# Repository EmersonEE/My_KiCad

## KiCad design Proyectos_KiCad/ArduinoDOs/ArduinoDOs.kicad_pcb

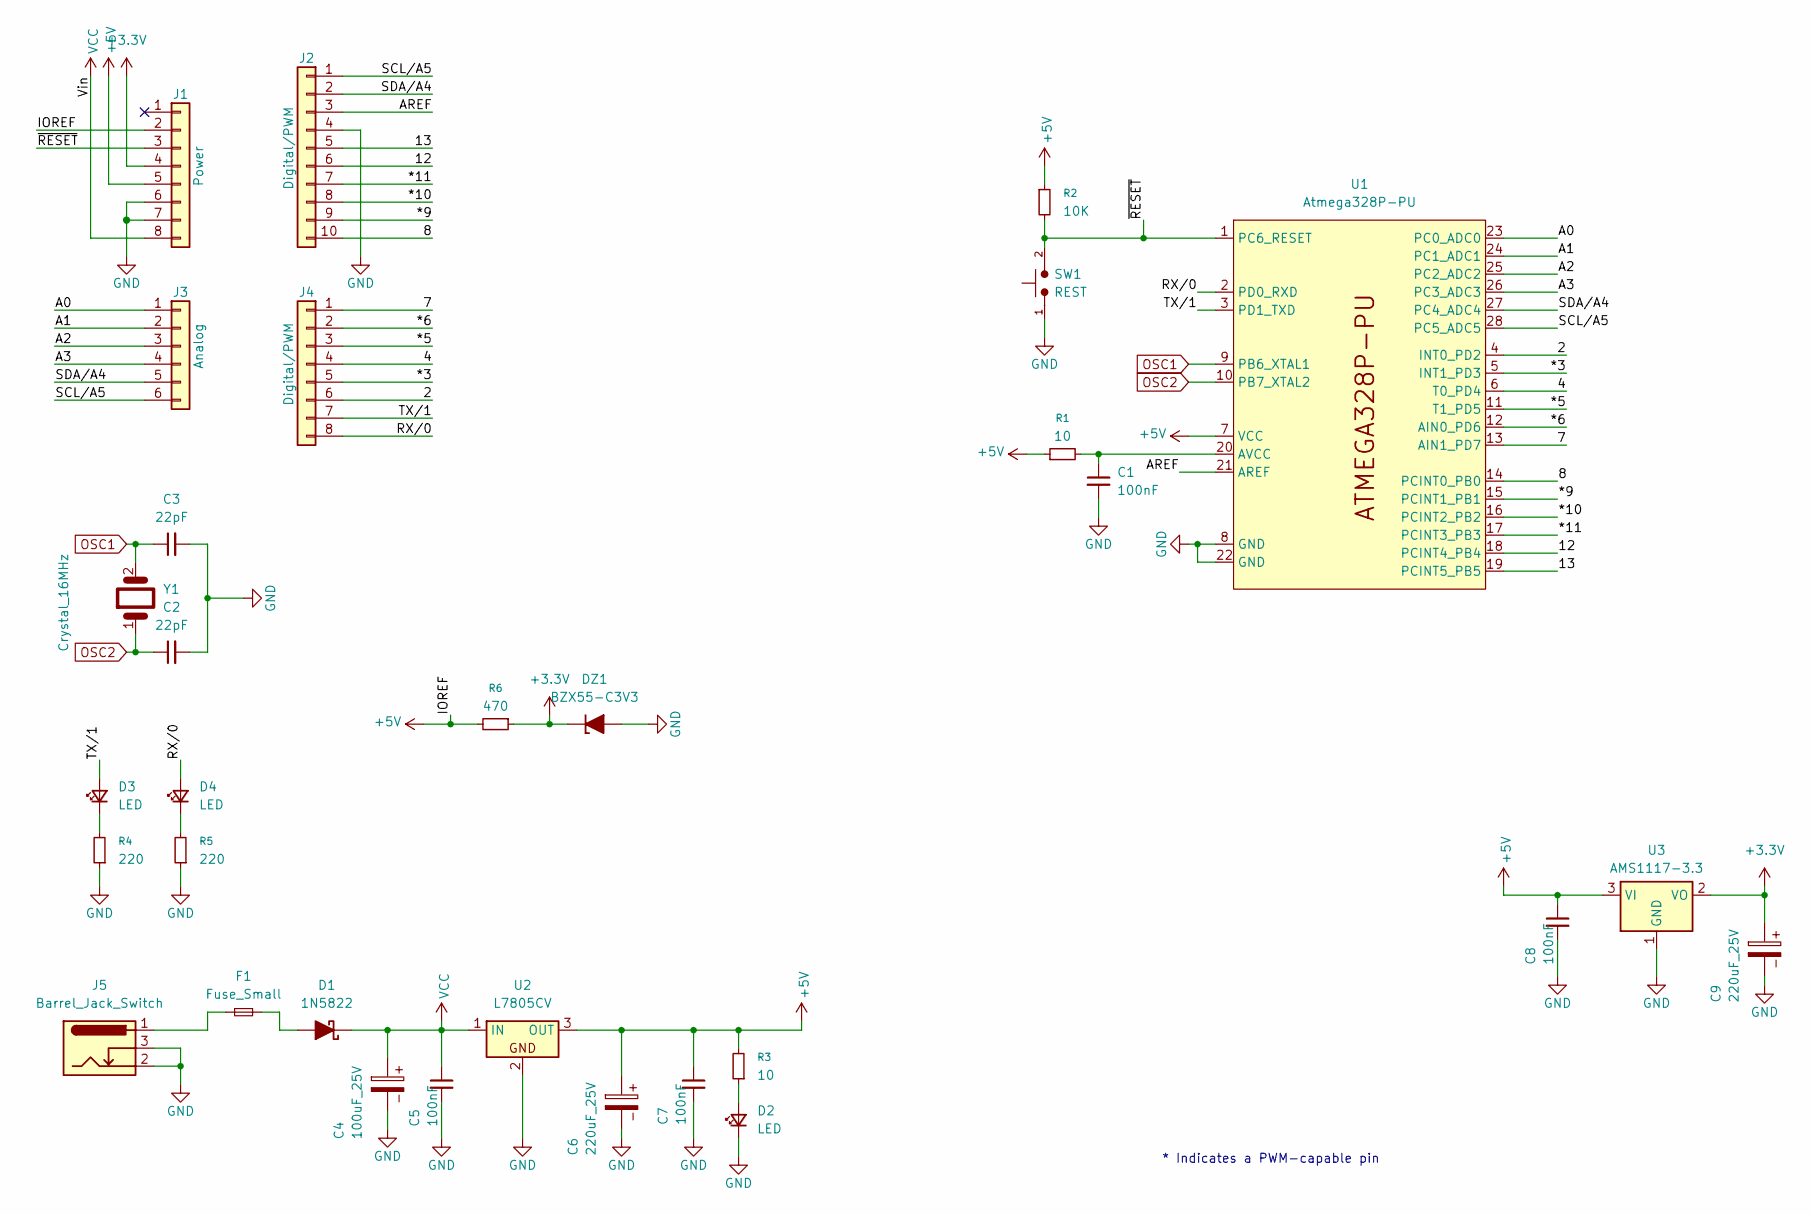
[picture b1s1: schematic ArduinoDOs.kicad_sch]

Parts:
C1, C5, C7, C8: 100nF; C_Disc_D4.7mm_W2.5mm_P5.00mm
C2, C3: 22pF; C_Disc_D4.7mm_W2.5mm_P5.00mm
C4: 100uF_25V; CP_Radial_D6.3mm_P2.50mm
C6, C9: 220uF_25V; CP_Radial_D8.0mm_P3.50mm
D1: 1N5822; D_DO-201AD_P12.70mm_Horizontal
D2, D3, D4: LED; LED_D5.0mm
DZ1: BZX55-C3V3; D_DO-35_SOD27_P7.62mm_Horizontal_Zener
F1: Fuse_Small; Fuse_BelFuse_0ZRE0033FF_L11.4mm_W3.8mm
J1: Power; PinSocket_1x08_P2.54mm_Vertical
J2: Digital/PWM; PinSocket_1x10_P2.54mm_Vertical
J3: Analog; PinSocket_1x06_P2.54mm_Vertical
J4: Digital/PWM; PinSocket_1x08_P2.54mm_Vertical
J5: Barrel_Jack_Switch; BarrelJack_GCT_DCJ200-10-A_Horizontal
R1, R3: 10; R_Axial_DIN0207_L6.3mm_D2.5mm_P10.16mm_Horizontal
R2: 10K; R_Axial_DIN0207_L6.3mm_D2.5mm_P10.16mm_Horizontal
R4, R5: 220; R_Axial_DIN0207_L6.3mm_D2.5mm_P10.16mm_Horizontal
R6: 470; R_Axial_DIN0207_L6.3mm_D2.5mm_P10.16mm_Horizontal
SW1: REST; SW_PUSH_6mm
U1: Atmega328P-PU; CERDIP-28_W7.62mm_SideBrazed_LongPads
U2: L7805CV; TO-220-3_Vertical
U3: AMS1117-3.3; SOT-223-3_TabPin2
Y1: Crystal_16MHz; Crystal_HC49-4H_Vertical

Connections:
+3.3V: C9.1, DZ1.1 (K), J1.4, R6.1, U3.2 (VO)
+5V: C6.1, C7.1, C8.1, J1.2, J1.5, R1.1, R2.1, R3.2, R6.2, U1.7 (VCC), U2.3 (OUT), U3.3 (VI)
/2: J4.6, U1.4 (INT0_PD2)
/4: J4.4, U1.6 (T0_PD4)
/7: J4.1, U1.13 (AIN1_PD7)
/8: J2.10, U1.14 (PCINT0_PB0)
/12: J2.6, U1.18 (PCINT4_PB4)
/13: J2.5, U1.19 (PCINT5_PB5)
/*3: J4.5, U1.5 (INT1_PD3)
/*5: J4.3, U1.11 (T1_PD5)
/*6: J4.2, U1.12 (AIN0_PD6)
/*9: J2.9, U1.15 (PCINT1_PB1)
/*10: J2.8, U1.16 (PCINT2_PB2)
/*11: J2.7, U1.17 (PCINT3_PB3)
/A0: J3.1, U1.23 (PC0_ADC0)
/A1: J3.2, U1.24 (PC1_ADC1)
/A2: J3.3, U1.25 (PC2_ADC2)
/A3: J3.4, U1.26 (PC3_ADC3)
/AREF: J2.3, U1.21 (AREF)
/RX/0: D4.2 (A), J4.8, U1.2 (PD0_RXD)
/SCL/A5: J2.1, J3.6, U1.28 (PC5_ADC5)
/SDA/A4: J2.2, J3.5, U1.27 (PC4_ADC4)
/TX/1: D3.2 (A), J4.7, U1.3 (PD1_TXD)
/~RESET: J1.3, R2.2, SW1.2, U1.1 (PC6_RESET)
GND: C1.2, C2.2, C3.2, C4.2, C5.2, C6.2, C7.2, C8.2, C9.2, D2.1 (K), DZ1.2 (A), J1.6, J1.7, J2.4, J5.2, J5.3, R4.1, R5.1, SW1.1, U1.8 (GND), U1.22 (GND), U2.2, U3.1 (GND)
unnamed: D1.2 (A), F1.2
unnamed: D2.2 (A), R3.1
unnamed: D3.1 (K), R4.2
unnamed: D4.1 (K), R5.2
unnamed: F1.1, J5.1
unnamed: C1.1, R1.2, U1.20 (AVCC)
OSC1: C3.1, U1.9 (PB6_XTAL1), Y1.2
OSC2: C2.1, U1.10 (PB7_XTAL2), Y1.1
VCC: C4.1, C5.1, D1.1 (K), J1.8, U2.1 (IN)

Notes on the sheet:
* Indicates a PWM-capable pin

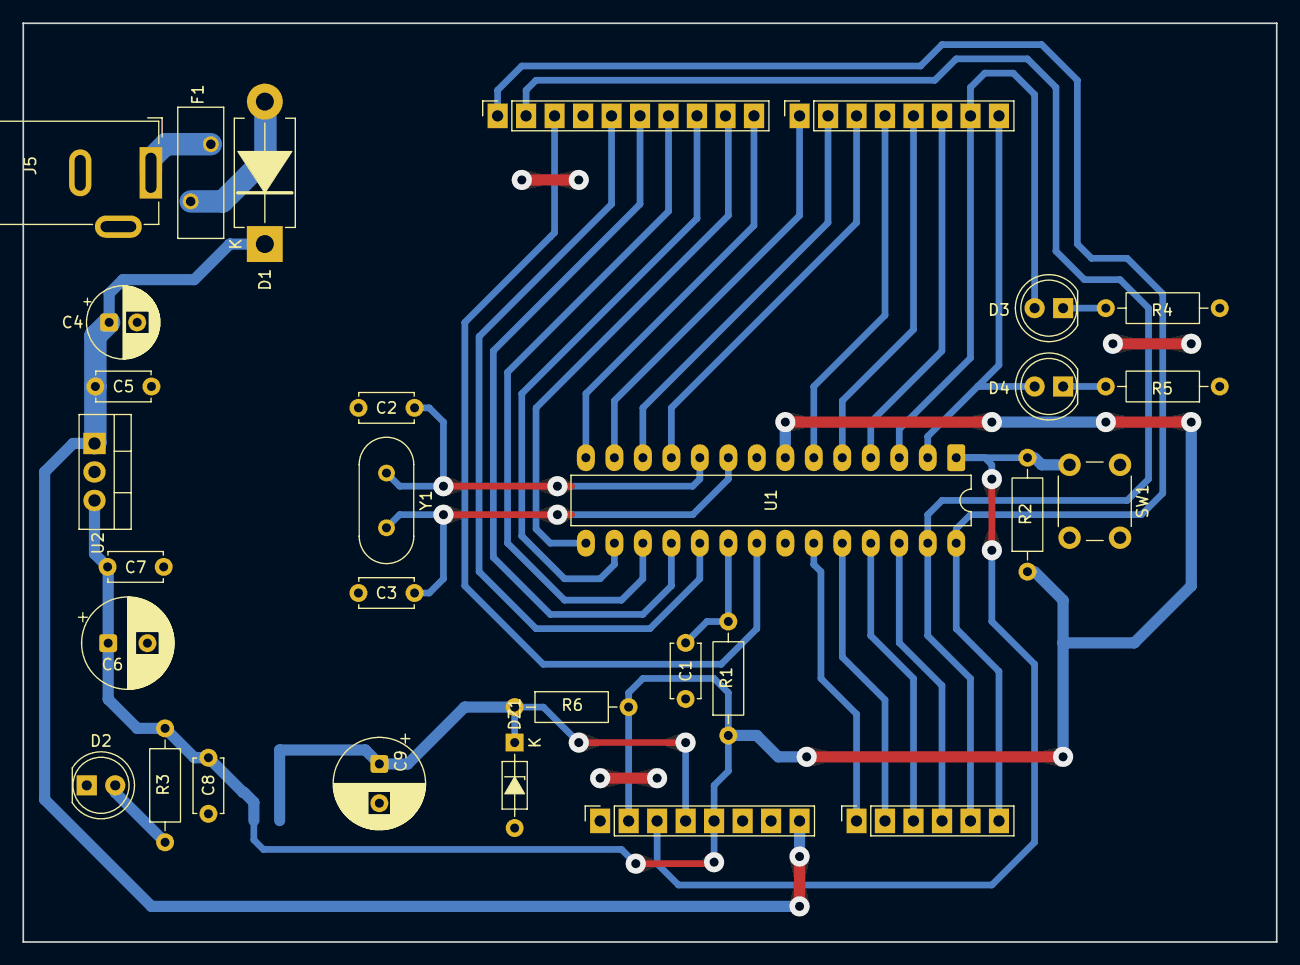
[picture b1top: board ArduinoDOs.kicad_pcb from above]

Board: 2 copper layers, 111.8 x 81.9 mm, 31 parts (1 on the bottom side), 34 nets.

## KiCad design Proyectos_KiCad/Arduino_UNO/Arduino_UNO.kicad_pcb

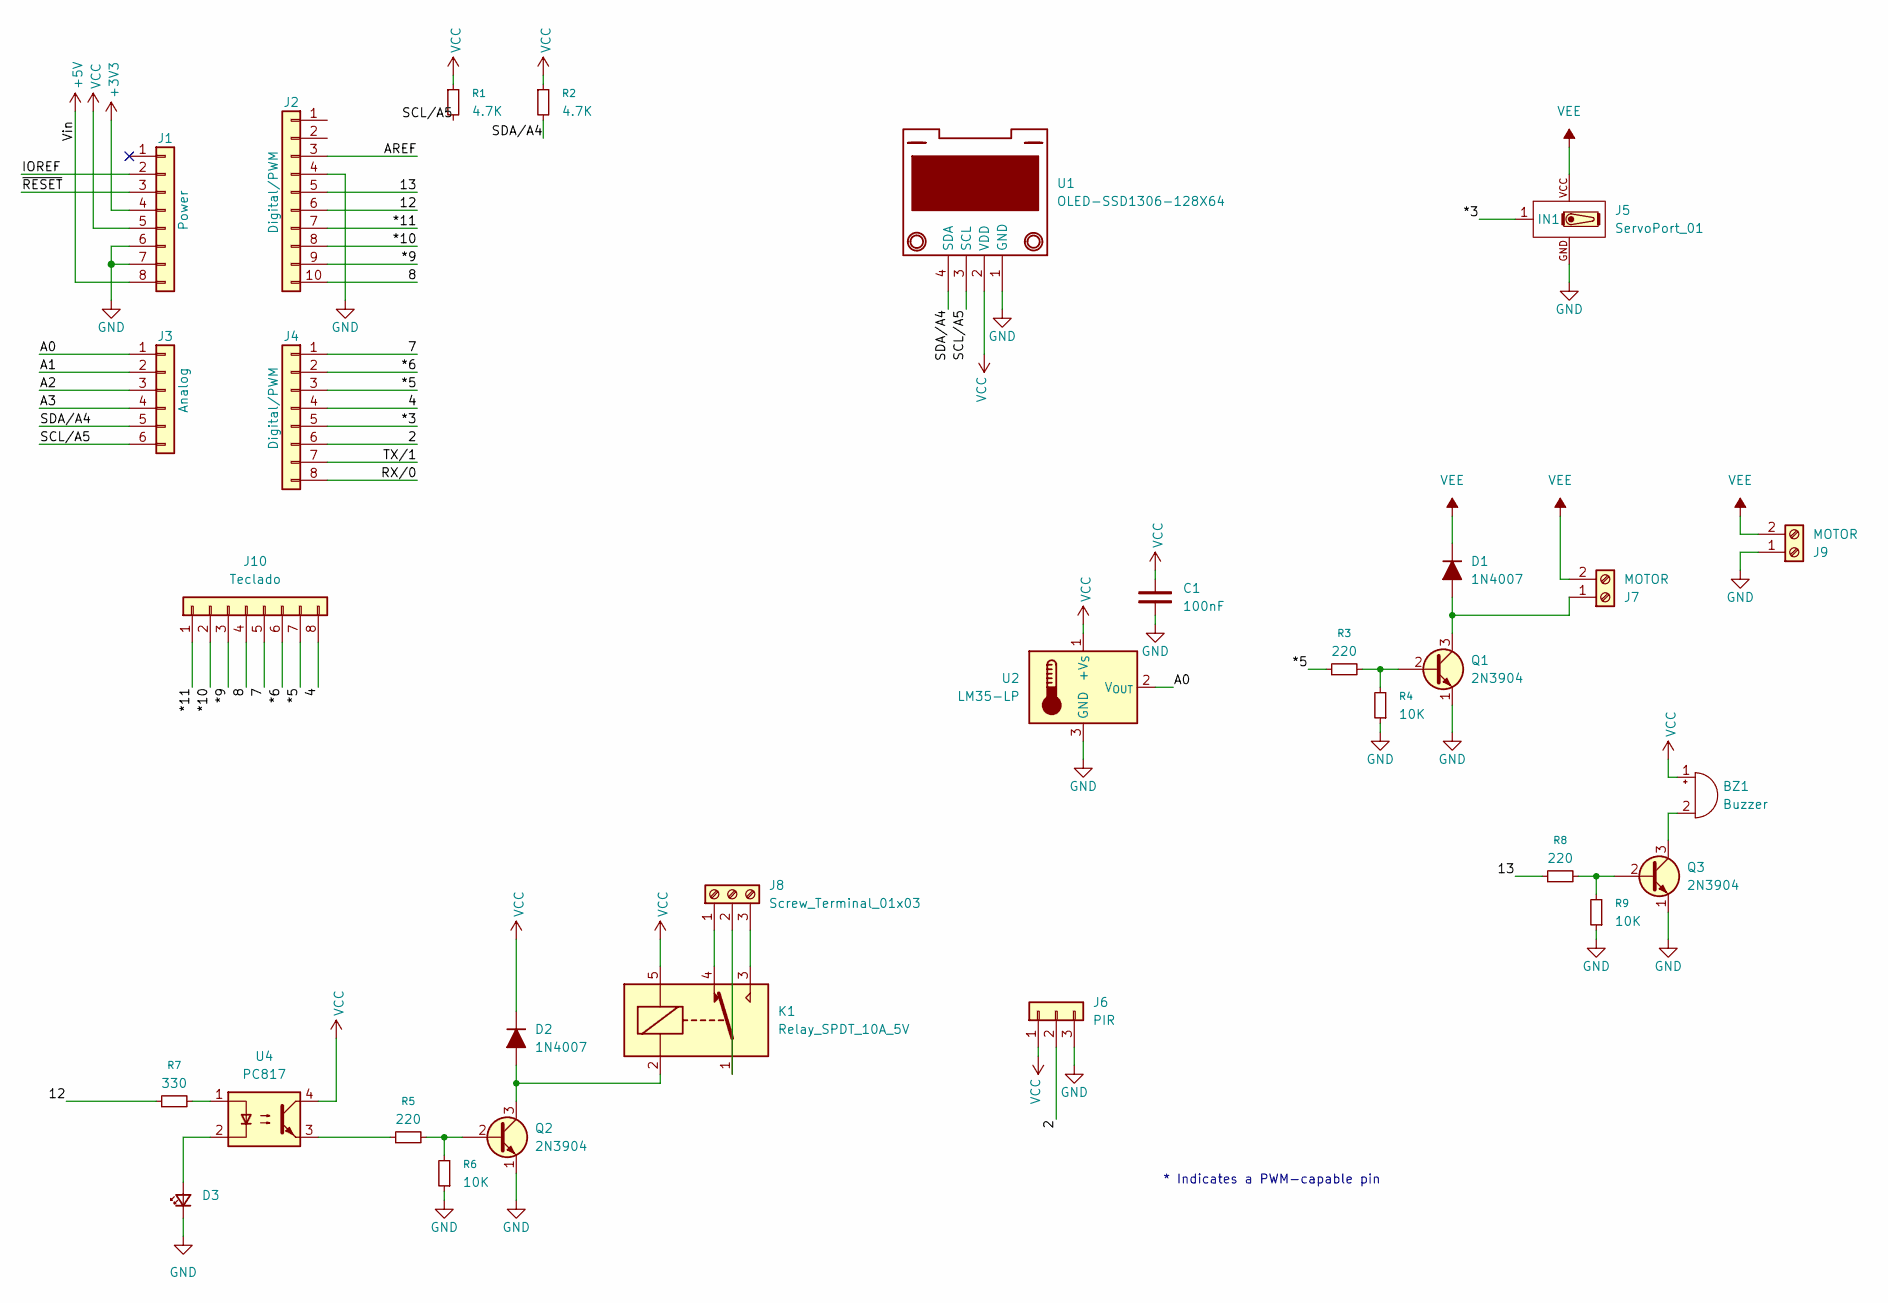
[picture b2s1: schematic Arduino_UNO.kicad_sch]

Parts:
BZ1: Buzzer; MagneticBuzzer_ProSignal_ABT-410-RC
C1: 100nF; C_Disc_D5.0mm_W2.5mm_P2.50mm
D1, D2: 1N4007; D_DO-41_SOD81_P7.62mm_Horizontal
D3: LED_D5.0mm
J1: Power; PinHeader_1x08_P2.54mm_Vertical
J2: Digital/PWM; PinHeader_1x10_P2.54mm_Vertical
J3: Analog; PinHeader_1x06_P2.54mm_Vertical
J4: Digital/PWM; PinHeader_1x08_P2.54mm_Vertical
J5: ServoPort_01; ServoPort_01_Vertical
J6: PIR; PinHeader_1x03_P2.54mm_Vertical
J7, J9: MOTOR; TerminalBlock_Phoenix_MKDS-1,5-2-5.08_1x02_P5.08mm_Horizont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
J8: Screw_Terminal_01x03; TerminalBlock_Phoenix_MKDS-1,5-3_1x03_P5.00mm_Horizontal
J10: Teclado; PinHeader_1x08_P2.54mm_Vertical
K1: Relay_SPDT_10A_5V; Relay_SPDT_10A_15.2x19.0mm
Q1, Q2, Q3: 2N3904; TO-92_Inline_Wide_EBC
R1, R2: 4.7K; 2.2
R3, R5, R8: 220; 2.2
R4, R6, R9: 10K; 2.2
R7: 330; 2.2
U1: OLED-SSD1306-128X64; SSD1306
U2: LM35-LP; TO-92L_Inline_Wide
U4: PC817; DIP-4_W7.62mm

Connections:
+3V3: J1.4
+5V: J1.8
/2: J4.6, J6.2
/4: J4.4, J10.8
/7: J4.1, J10.5
/8: J2.10, J10.4
/12: J2.6, R7.1
/13: J2.5, R8.1
/*3: J4.5, J5.1 (IN1_1)
/*5: J4.3, J10.7, R3.1
/*6: J4.2, J10.6
/*9: J2.9, J10.3
/*10: J2.8, J10.2
/*11: J2.7, J10.1
/A0: J3.1, U2.2 (V_{OUT})
/A1: J3.2
/A2: J3.3
/A3: J3.4
/AREF: J2.3
/IOREF: J1.2
/RX/0: J4.8
/SCL/A5: J3.6, R1.2, U1.3 (SCL)
/SDA/A4: J3.5, R2.2, U1.4 (SDA)
/TX/1: J4.7
/~RESET: J1.3
GND: C1.1, D3.1 (K), J1.6, J1.7, J2.4, J5.GND, J6.3, J9.1, Q1.1 (E), Q2.1 (E), Q3.1 (E), R4.1, R6.1, R9.1, U1.1 (GND), U2.3 (GND)
unnamed: BZ1.2 (-), Q3.3 (C)
unnamed: D1.2 (A), J7.1, Q1.3 (C)
unnamed: D2.2 (A), K1.2, Q2.3 (C)
unnamed: D3.2 (A), U4.2
unnamed: J8.1, K1.4
unnamed: J8.2, K1.1
unnamed: J8.3, K1.3
unnamed: Q1.2 (B), R3.2, R4.2
unnamed: Q2.2 (B), R5.2, R6.2
unnamed: Q3.2 (B), R8.2, R9.2
unnamed: R5.1, U4.3
unnamed: R7.2, U4.1
VCC: BZ1.1 (+), C1.2, D2.1 (K), J1.5, J6.1, K1.5, R1.1, R2.1, U1.2 (VDD), U2.1 (+V_{S}), U4.4
VEE: D1.1 (K), J5.VCC, J7.2, J9.2

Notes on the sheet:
* Indicates a PWM-capable pin

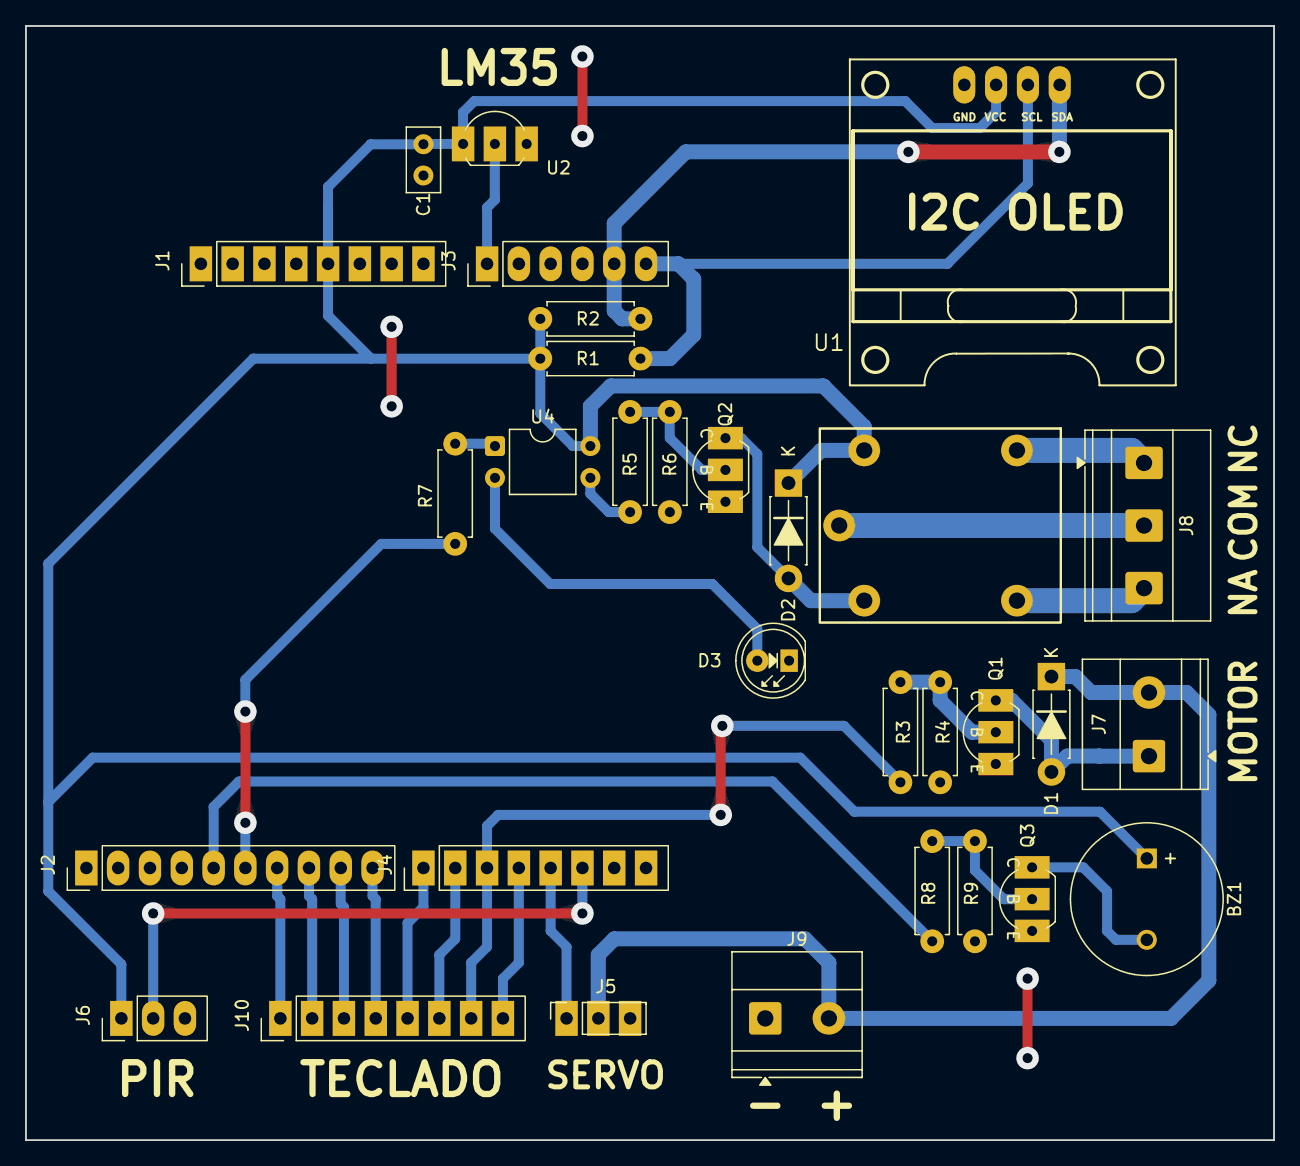
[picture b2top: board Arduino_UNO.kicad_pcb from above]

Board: 2 copper layers, 99.7 x 89.0 mm, 31 parts (0 on the bottom side), 30 nets.

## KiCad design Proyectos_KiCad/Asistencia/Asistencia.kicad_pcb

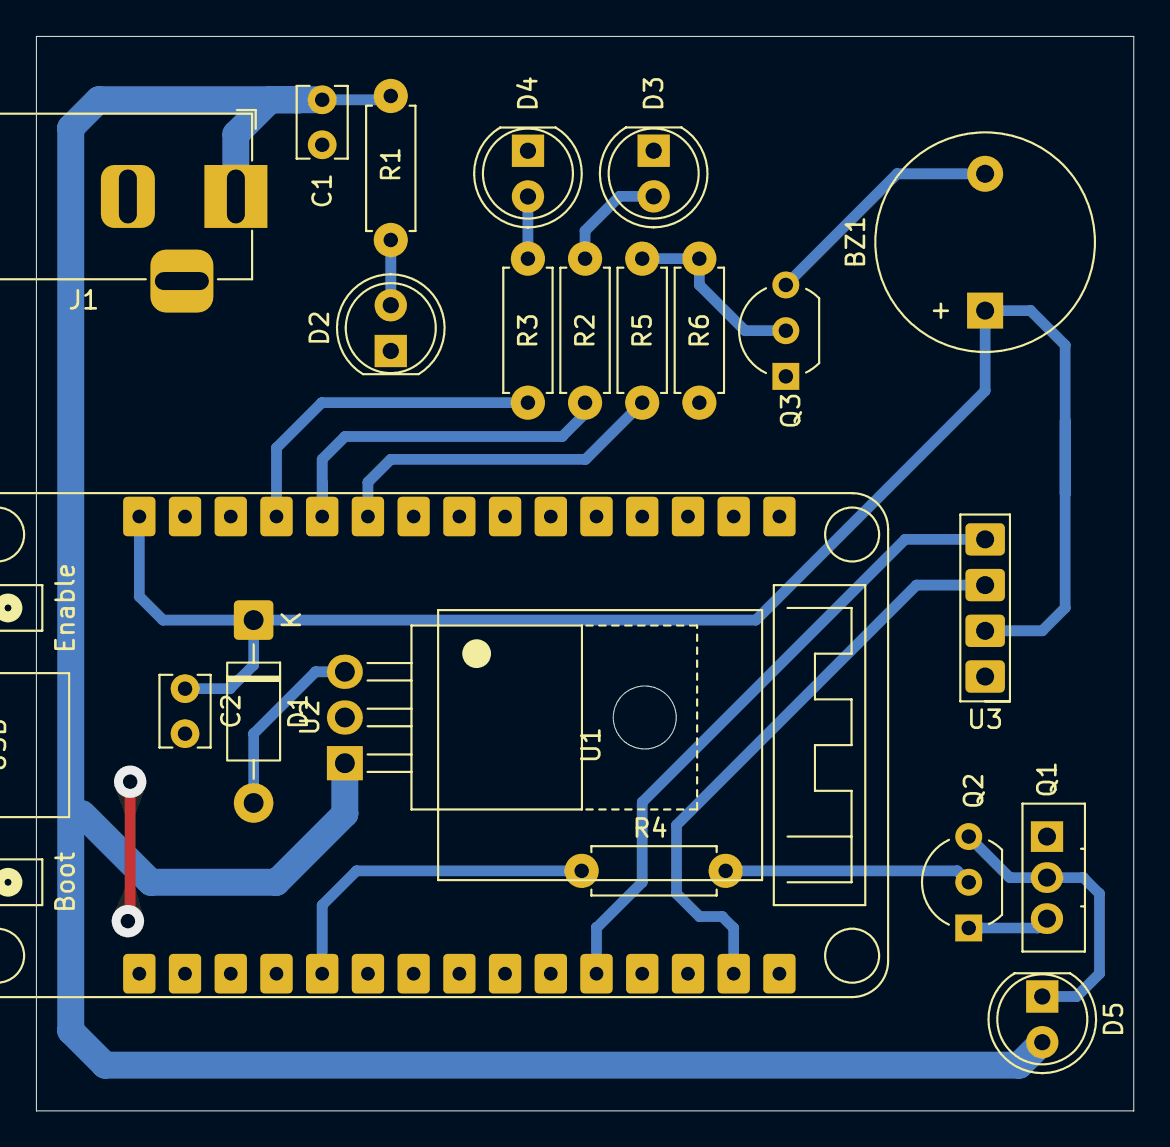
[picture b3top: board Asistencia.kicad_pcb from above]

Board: 2 copper layers, 61.0 x 59.7 mm, 21 parts (0 on the bottom side), 18 nets.

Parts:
BZ1: Buzzer; Buzzer_12x9.5RM7.6
C1, C2: 100nF; C_Disc_D3.8mm_W2.6mm_P2.50mm
D1: 1N4007; D_DO-41_SOD81_P10.16mm_Horizontal
D2, D3, D4: LED_D5.0mm
D5: LED; LED_D5.0mm
J1: DC JACK; BarrelJack_Horizontal
Q1: BD139; TO-126-3_Vertical
Q2, Q3: 2N3904; TO-92_Inline_Wide
R1, R4: 1K
R2, R3: 470
R5: 2.2K
R6: 4.7K
U1: ESP32_DevKit_V1_DOIT; ESP32_DEVKIT_V1_E32
U2: LM7805_TO220; TO-220-3_Horizontal_TabUp
U3: SSD1306

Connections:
+5V: BZ1.1 (+), C2.1, D1.1 (K), U1.15 (VIN), U3.2 (VCC)
BUZZER: R5.1, U1.10 (D27/GPIO27/ADC2/TOUCH7)
GND: C1.2, C2.2, D2.1 (K), D3.1 (K), D4.1 (K), J1.2, J1.3, Q1.1 (E), Q3.1 (E), R6.1, U1.14 (GND), U1.17 (GND), U2.2 (GND), U3.1 (GND)
LED_ERROR: R3.1, U1.12 (D12/GPIO12/ADC2/TOUCH5)
LED_OK: R2.1, U1.11 (D14/GPIO14/ADC2/TOUCH6)
unnamed: BZ1.2 (-), Q3.3 (C)
unnamed: D1.2 (A), U2.3 (VO)
unnamed: D2.2 (A), R1.2
unnamed: D3.2 (A), R2.2
unnamed: D4.2 (A), R3.2
unnamed: D5.1 (K), Q1.2 (C), Q2.3 (C)
unnamed: Q1.3 (B), Q2.1 (E)
unnamed: Q2.2 (B), R4.2
unnamed: Q3.2 (B), R5.2, R6.2
PWM_LED: R4.1, U1.20 (TOUCH0/ADC2/GPIO4/D4)
SCL: U1.29 (SCL/GPIO22/D22), U3.3 (SCL)
SDA: U1.26 (SDA/GPIO21/D21), U3.4 (SDA)
VCC: C1.1, D5.2 (A), J1.1, R1.1, U2.1 (VI)

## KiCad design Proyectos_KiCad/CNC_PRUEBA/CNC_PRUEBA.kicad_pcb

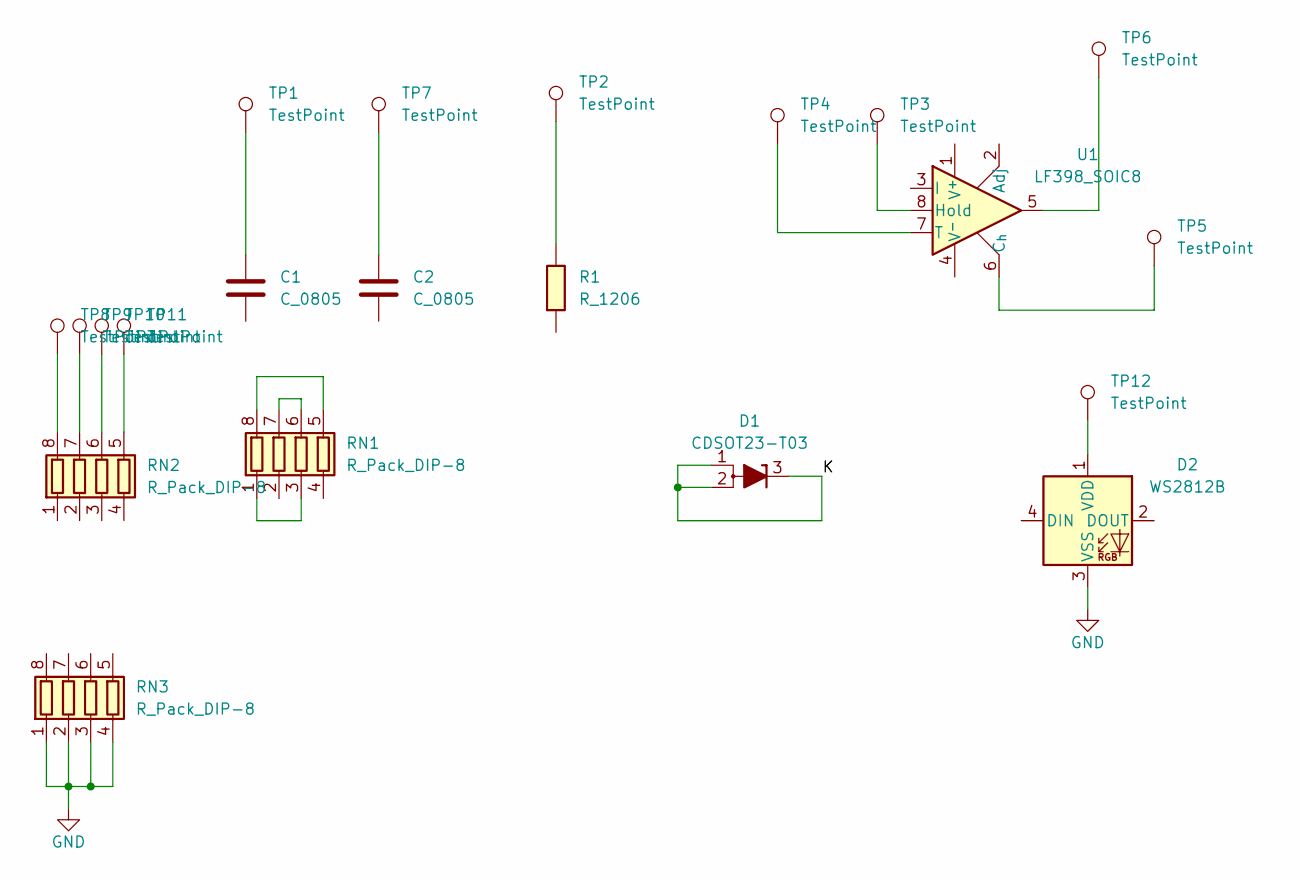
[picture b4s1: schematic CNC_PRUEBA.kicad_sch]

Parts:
C1, C2: C_0805; C_0805_2012Metric
D1: CDSOT23-T03; SOT-23
D2: WS2812B; LED_WS2812B_PLCC4_5.0x5.0mm_P3.2mm
R1: R_1206
RN1, RN2, RN3: R_Pack_DIP-8; DIP-8_W7.62mm_LongPads
TP1, TP2, TP3, TP4, TP5, TP6, TP7, TP8, TP9, TP10, TP11, TP12: TestPoint; Pin_D0.7mm_L6.5mm_W1.8mm_FlatFork
U1: LF398_SOIC8; SOIC-8_3.9x4.9mm_P1.27mm

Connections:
/K: D1.1 (A), D1.2 (A), D1.3 (K)
GND: D2.3 (VSS), RN3.1 (R1.1), RN3.2 (R2.1), RN3.3 (R3.1), RN3.4 (R4.1)
unnamed: C1.1, TP1.1 (1_1)
unnamed: C2.1, TP7.1 (1_1)
unnamed: D2.1 (VDD), TP12.1 (1_1)
unnamed: R1.1, TP2.1 (1_1)
unnamed: RN1.1 (R1.1), RN1.3 (R3.1)
unnamed: RN1.5 (R4.2), RN1.8 (R1.2)
unnamed: RN1.6 (R3.2), RN1.7 (R2.2)
unnamed: RN2.8 (R1.2), TP8.1 (1_1)
unnamed: RN2.7 (R2.2), TP9.1 (1_1)
unnamed: RN2.6 (R3.2), TP10.1 (1_1)
unnamed: RN2.5 (R4.2), TP11.1 (1_1)
unnamed: TP6.1 (1_1), U1.5
unnamed: TP5.1 (1_1), U1.6 (C_{h})
unnamed: TP3.1 (1_1), U1.8 (Hold)
unnamed: TP4.1 (1_1), U1.7 (T)

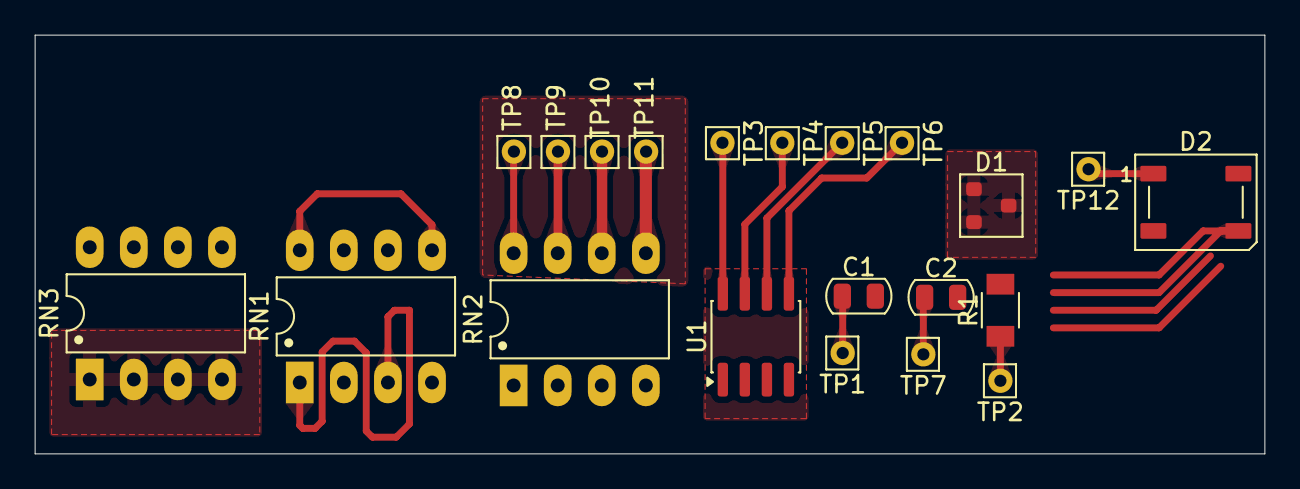
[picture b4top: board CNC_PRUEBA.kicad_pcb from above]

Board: 2 copper layers, 70.9 x 24.1 mm, 21 parts (0 on the bottom side), 17 nets.

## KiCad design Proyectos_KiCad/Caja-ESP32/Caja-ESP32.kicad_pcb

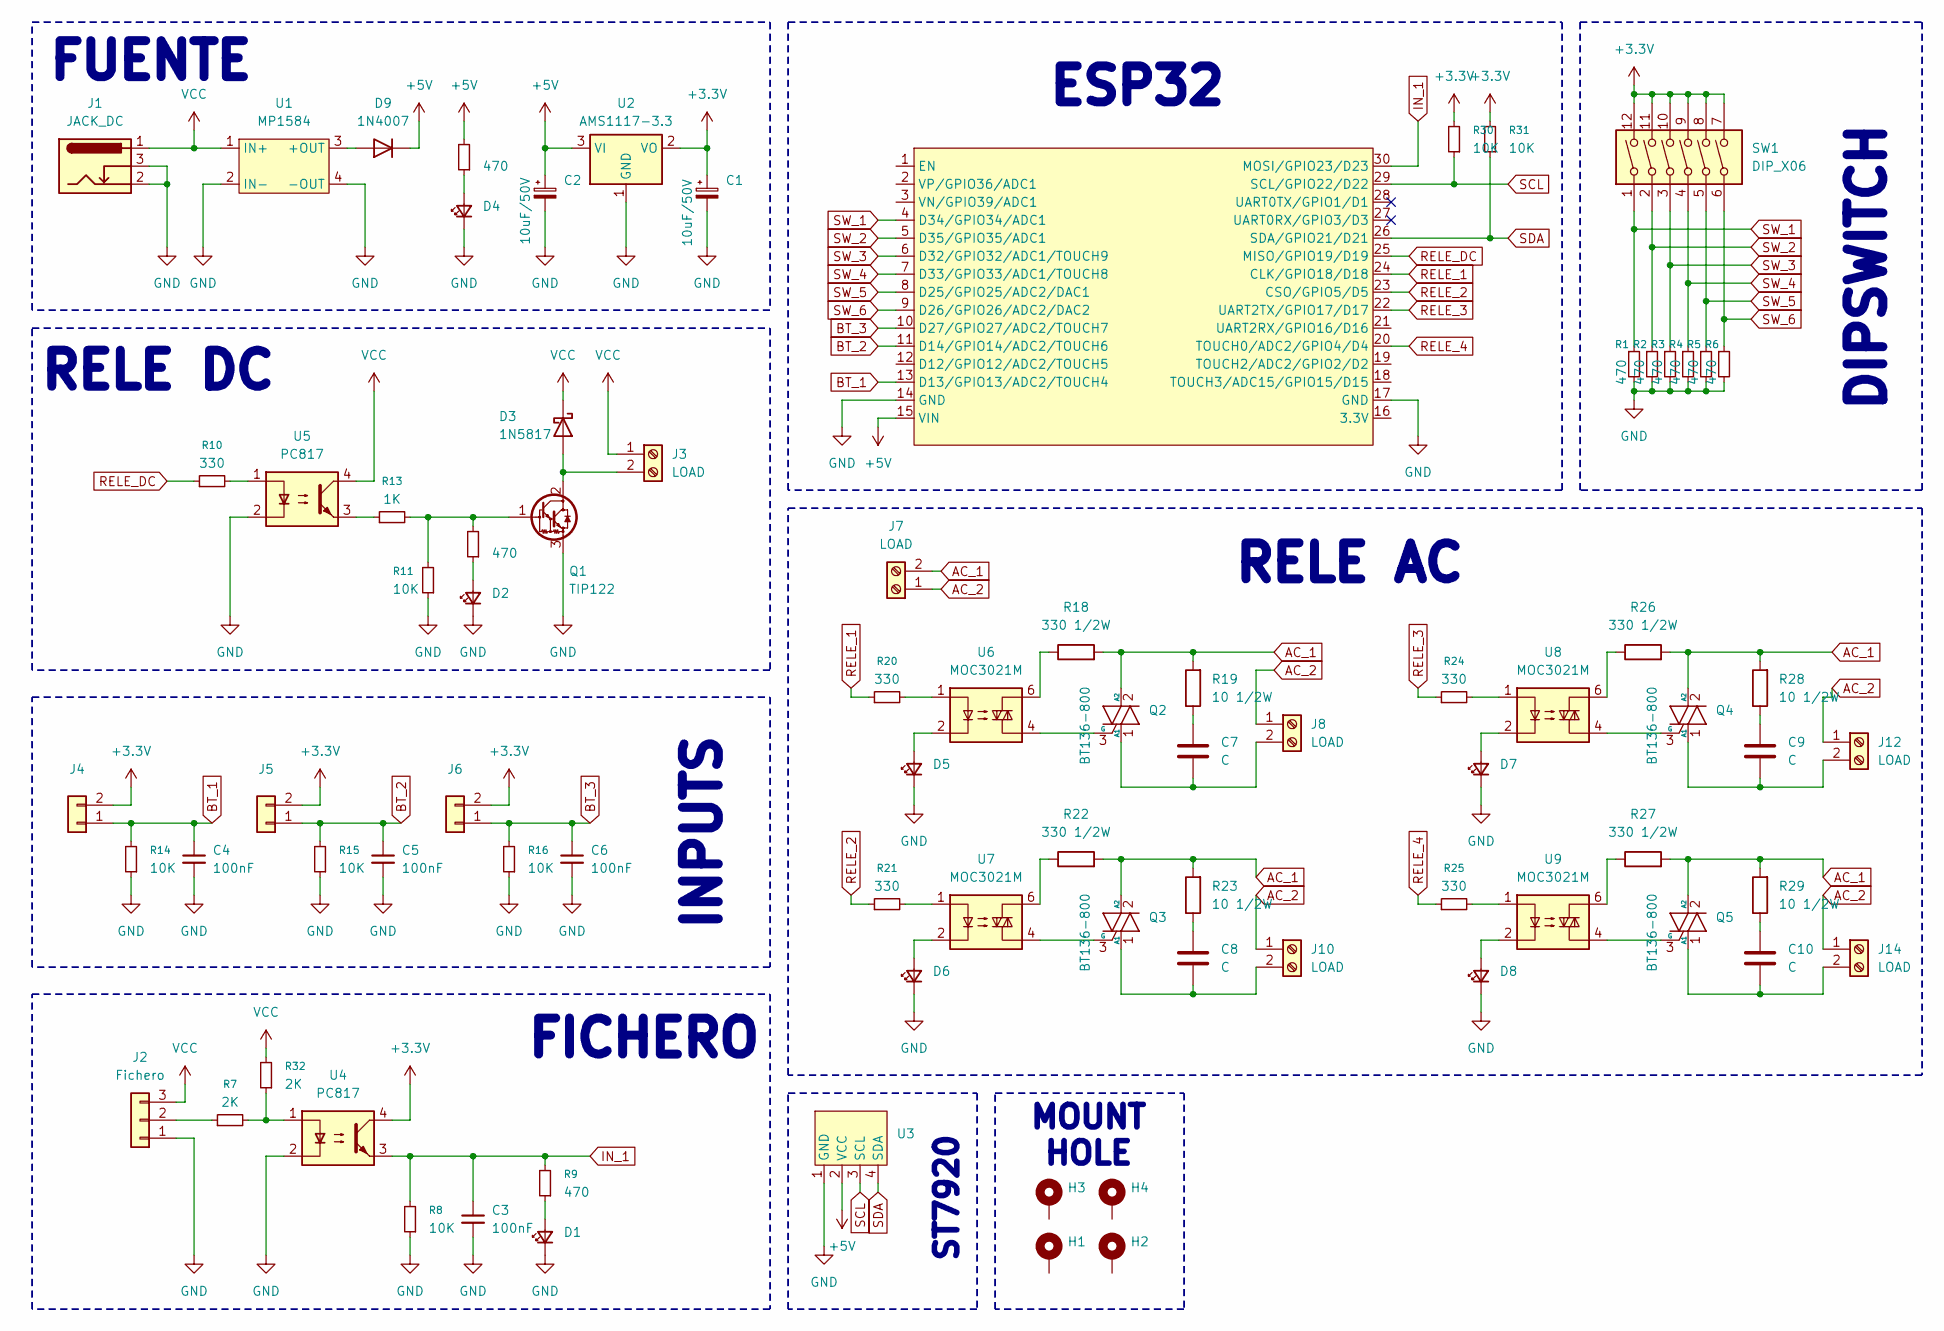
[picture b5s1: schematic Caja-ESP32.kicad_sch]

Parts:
C1, C2: 10uF/50V; CP_Radial_D4.0mm_P2.00mm
C3, C4, C5, C6: 100nF; C_Disc_D3.8mm_W2.6mm_P2.50mm
C7, C8, C9, C10: C; C_Rect_L10.3mm_W5.0mm_P7.50mm_MKS4
D1, D2, D4: LED_D5.0mm
D3: 1N5817; D_DO-41_SOD81_P10.16mm_Horizontal
D5: LED_B5.0mm
D6: LED_G5.0mm
D7: LED_O5.0mm
D8: LED_Y5.0mm
D9: 1N4007; D_DO-41_SOD81_P10.16mm_Horizontal
H1, H2, H3, H4: MountingHole_3.2mm_M3_Pad_Via
J1: JACK_DC; BarrelJack_GCT_DCJ200-10-A_Horizontal
J2: Fichero; Molex_KK-254_AE-6410-03A_1x03_P2.54mm_Vertical
J3, J7, J8, J10, J12, J14: LOAD; TerminalBlock_Phoenix_MKDS-1,5-2-5.08_1x02_P5.08mm_Horizont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
J4, J5, J6: Molex_KK-254_AE-6410-02A_1x02_P2.54mm_Vertical
Q1: TIP122; TO-220-3_Vertical
Q2, Q3, Q4, Q5: BT136-800; TO-220-3_Vertical
R1, R2, R3, R4, R5, R6, R9, R12, R17: 470
R7, R32: 2K
R8, R11, R14, R15, R16, R30, R31: 10K
R10, R20, R21, R24, R25: 330
R13: 1K
R18, R22, R26, R27: 330 1/2W; R_Axial_DIN0207_L6.3mm_D2.5mm_P10.16mm_Horizontal
R19, R23, R28, R29: 10 1/2W; R_Axial_DIN0207_L6.3mm_D2.5mm_P10.16mm_Horizontal
SW1: DIP_X06; SW_DIP_SPSTx06_Slide_9.78x17.42mm_W7.62mm_P2.54mm
U1: MP1584; MP1584_Module
U2: AMS1117-3.3; SOT-223-3_TabPin2
U3: LCD ST7920
U4, U5: PC817; DIP-4_W7.62mm
U6, U7, U8, U9: MOC3021M; MOC3020
U10: ESP32_DevKit_V1_DOIT; ESP32_DEVKIT_V1_E32

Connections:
+3.3V: C1.1, J4.2, J5.2, J6.2, R30.2, R31.2, SW1.7, SW1.8, SW1.9, SW1.10, SW1.11, SW1.12, U2.2 (VO), U4.4
+5V: C2.1, D9.1 (K), R17.2, U2.3 (VI), U3.2 (VCC), U10.15 (VIN)
AC_1: J7.2, Q2.2 (A2), Q3.2 (A2), Q4.2 (A2), Q5.2 (A2), R18.2, R19.2, R22.2, R23.2, R26.2, R27.2, R28.2, R29.2
AC_2: J7.1, J8.1, J10.1, J12.1, J14.1
BT_1: C4.1, J4.1, R14.2, U10.13 (D13/GPIO13/ADC2/TOUCH4)
BT_2: C5.1, J5.1, R15.2, U10.11 (D14/GPIO14/ADC2/TOUCH6)
BT_3: C6.1, J6.1, R16.2, U10.10 (D27/GPIO27/ADC2/TOUCH7)
GND: C1.2, C2.2, C3.2, C4.2, C5.2, C6.2, D1.1 (K), D2.1 (K), D4.1 (K), D5.1 (K), D6.1 (K), D7.1 (K), D8.1 (K), J1.2, J1.3, J2.1, Q1.3 (E), R1.2, R2.2, R3.2, R4.2, R5.2, R6.2, R8.1, R11.1, R14.1, R15.1, R16.1, U1.2 (IN-), U1.4 (-OUT), U2.1 (GND), U3.1 (GND), U4.2, U5.2, U10.14 (GND), U10.17 (GND)
IN_1: C3.1, R8.2, R9.2, U4.3, U10.30 (MOSI/GPIO23/D23)
unnamed: C7.1, R19.1
unnamed: C8.1, R23.1
unnamed: C9.1, R28.1
unnamed: C10.1, R29.1
unnamed: D1.2 (A), R9.1
unnamed: D2.2 (A), R12.1
unnamed: D3.2 (A), J3.2, Q1.2 (C)
unnamed: D4.2 (A), R17.1
unnamed: D5.2 (A), U6.2
unnamed: D6.2 (A), U7.2
unnamed: D7.2 (A), U8.2
unnamed: D8.2 (A), U9.2
unnamed: D9.2 (A), U1.3 (+OUT)
unnamed: J2.2, R7.1
unnamed: C7.2, J8.2, Q2.1 (A1)
unnamed: C8.2, J10.2, Q3.1 (A1)
unnamed: C9.2, J12.2, Q4.1 (A1)
unnamed: C10.2, J14.2, Q5.1 (A1)
unnamed: Q1.1 (B), R11.2, R12.2, R13.2
unnamed: Q2.3 (G), U6.4
unnamed: Q3.3 (G), U7.4
unnamed: Q4.3 (G), U8.4
unnamed: Q5.3 (G), U9.4
unnamed: R10.2, U5.1
unnamed: R13.1, U5.3
unnamed: R18.1, U6.6
unnamed: R20.2, U6.1
unnamed: R21.2, U7.1
unnamed: R22.1, U7.6
unnamed: R24.2, U8.1
unnamed: R25.2, U9.1
unnamed: R26.1, U8.6
unnamed: R27.1, U9.6
unnamed: R7.2, R32.1, U4.1
RELE_1: R20.1, U10.24 (CLK/GPIO18/D18)
RELE_2: R21.1, U10.23 (CSO/GPIO5/D5)
RELE_3: R24.1, U10.22 (UART2TX/GPIO17/D17)
RELE_4: R25.1, U10.20 (TOUCH0/ADC2/GPIO4/D4)
RELE_DC: R10.1, U10.25 (MISO/GPIO19/D19)
SCL: R30.1, U3.3 (SCL), U10.29 (SCL/GPIO22/D22)
SDA: R31.1, U3.4 (SDA), U10.26 (SDA/GPIO21/D21)
SW_1: R1.1, SW1.1, U10.4 (D34/GPIO34/ADC1)
SW_2: R2.1, SW1.2, U10.5 (D35/GPIO35/ADC1)
SW_3: R3.1, SW1.3, U10.6 (D32/GPIO32/ADC1/TOUCH9)
SW_4: R4.1, SW1.4, U10.7 (D33/GPIO33/ADC1/TOUCH8)
SW_5: R5.1, SW1.5, U10.8 (D25/GPIO25/ADC2/DAC1)
SW_6: R6.1, SW1.6, U10.9 (D26/GPIO26/ADC2/DAC2)
VCC: D3.1 (K), J1.1, J2.3, J3.1, R32.2, U1.1 (IN+), U5.4

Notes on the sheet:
RELE DC
MOUNT HOLE
ESP32
FUENTE
DIPSWITCH
FICHERO
ST7920
RELE AC
INPUTS

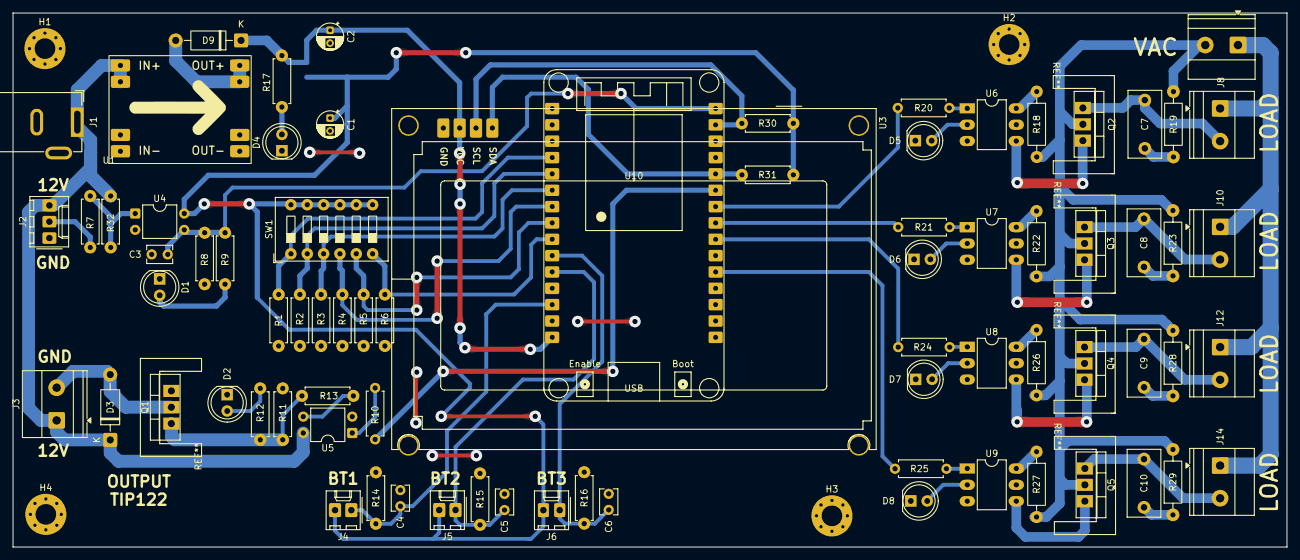
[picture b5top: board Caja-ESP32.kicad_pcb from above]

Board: 2 copper layers, 198.0 x 83.0 mm, 82 parts (1 on the bottom side), 57 nets.
